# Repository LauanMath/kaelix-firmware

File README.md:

# Kaelix

O Kaelix mede a vibração de motores industriais com um transmissor de baixo
custo, fixado na carcaça do motor, que envia o sinal pelo rádio LoRa a um
*gateway* instalado no mesmo local. Este repositório guarda o *firmware* dos
dois dispositivos, os dados da coleta em campo de 2 de novembro de 2026 e as
análises de detecção de falhas feitas com esses dados e com uma base pública de
laboratório. A interface de programação de aplicações (API), o banco de dados e
o aplicativo de mesa que recebem os dados do *gateway* estão no repositório
[kaelix-industrial-intelligence](https://github.com/LauanMath/kaelix-industrial-intelligence).

O sistema foi desenvolvido no trabalho de conclusão de curso de Lauan Matheus
da Rocha Alves, em Engenharia de Software, no Instituto de Ensino Superior
iCEV, em 2026. A monografia está em [`docs/monografia/`](docs/monografia/).

## Sistema

O transmissor usa o microcontrolador ESP32-C3, o módulo MPU-6050, com
acelerômetro e giroscópio de três eixos, e o rádio Ra-02 (circuito SX1278) em
433 MHz. Em cada ciclo de medição, ele adquire uma janela de 512 amostras por
eixo a 1 kHz e envia pelo rádio uma telemetria, com indicadores calculados
sobre a janela e o estado do dispositivo. Quando o *gateway* autoriza, o
transmissor envia também a janela de sinal bruto dos seis canais, dividida em
26 fragmentos, e essa sequência de fragmentos é chamada de rajada. O *gateway*
informa quais fragmentos recebeu, e o transmissor reenvia só os ausentes, em
até três tentativas.

O *gateway* usa o ESP32-S3, com outro rádio Ra-02 e Wi-Fi, e envia os dados à
API por HTTPS, pela rede local. Cada telemetria e cada janela ficam gravadas na
memória *flash* do *gateway* até que a API confirme o recebimento. O
transmissor recebe pelo rádio, por meio do *gateway*, a configuração, a rotina
de medição e os comandos definidos no aplicativo. O *gateway* é configurado
pela rede Wi-Fi própria (`Kaelix-XXXX`) e recebe atualizações de *firmware*
pela rede; o transmissor só recebe *firmware* por cabo.

| Parte | Código | Ambiente do PlatformIO |
|---|---|---|
| Transmissor | `src/transmitter/`, `src/sensors/`, `src/power/` | `kaelix-transmitter` |
| *Gateway* | `src/gateway/`, com a pinagem e o *buffer* de logs de `src/receiver/` | `kaelix-gateway` |
| Protocolo de rádio v3 e CRC | `lib/kaelix_protocol/`, `lib/crc16/` | os dois |
| Processamento de sinal e códigos de estado | `lib/signal_processing/`, `lib/kaelix_status/` | transmissor |

## Compilação e gravação

Os dois ambientes compilam com o PlatformIO, na plataforma `espressif32` com o
*framework* Arduino, e o rádio usa a biblioteca RadioLib 7.7.1:

```bash
pio run -e kaelix-transmitter -t upload --upload-port <porta>
pio run -e kaelix-gateway -t upload --upload-port <porta>
```

O `platformio.ini` é o mesmo que compilou o *firmware* da coleta, em 2 de
novembro de 2026, e não foi editado depois. O resumo SHA-256 dele e dos fontes
do transmissor e do *gateway* identifica essa versão
([`build_sistema_values.py`](docs/monografia/latex/scripts/build_sistema_values.py)).
Por isso, o arquivo ainda declara sete ambientes de versões anteriores
(`esp32-s3`, `esp32-s3-bench`, `lora-probe`, `esp32-s3-gateway`,
`esp32-c3-device`, `esp32-c3-receiver` e `lora-probe-c3`), cujo código foi
removido do repositório. Os ambientes antigos não compilam, e `pio run` sem
`-e` termina com erro ao chegar a eles. O `kaelix-gateway` herda do `esp32-s3`
as configurações da placa.

## Testes

Os testes do *firmware* rodam no computador, sem os dispositivos:

```bash
pio test -e native
```

As sete suítes somam 64 casos e cobrem o protocolo, os registros e o gravador
do *gateway*, o *buffer* de logs, o CRC, o processamento de sinal e a aquisição
de vibração. A saída da execução de 7 de novembro de 2026, sobre o mesmo código
da coleta, está em `experiments/sistema/`.

## Dados e análises

A coleta em campo de 2 de novembro de 2026 mediu quatro máquinas de uma
instalação industrial em operação normal: uma dobradeira, uma guilhotina
hidráulica, uma calandra piramidal e um compressor de parafuso. Os dados foram
exportados do banco da API em modo somente leitura e estão em
`experiments/campo/dados/`. O resumo SHA-256 de `ensaios.csv`, `leituras.csv`,
`janelas.csv` e `janelas.npz` foi gravado no registro das hipóteses antes de
qualquer cálculo
([`registro_v1.md`](docs/monografia/registro/registro_v1.md)). O banco e os
registros dos ensaios ficam fora do repositório, porque trazem nomes de rede e
endereços do local, e por isso os scripts de exportação não rodam a partir
dele.

As hipóteses H1 a H3, avaliadas nos dados de campo, foram registradas em 6 de
novembro de 2026, antes do cálculo. Emendas datadas, também anteriores aos
cálculos que definem, acrescentaram a hipótese H4, avaliada na base pública de
desbalanceamento da Fraunhofer-Gesellschaft, e as análises posteriores AP1 a
AP6 (registros v2 a v4, em [`docs/monografia/registro/`](docs/monografia/registro/)).

| Script | Análise | Saídas |
|---|---|---|
| `experiments/campo/analise_registrada.py` | H1 a H3 | `experiments/campo/analise_registrada/` |
| `experiments/campo/analise_descritiva.py` | ruído do sensor, rotação, espectros, rajadas e resposta a mudanças de condição | `experiments/campo/analise_descritiva/` |
| `experiments/campo/analise_posterior.py` | AP1 e AP2 | `experiments/campo/analise_posterior/` |
| `experiments/fraunhofer/baixar_membros_v2.py` | download dos seis arquivos da base usados em H4, com conferência de CRC-32 e tamanho | `experiments/fraunhofer/dados/v2/`, fora do git |
| `experiments/fraunhofer/analise_h4.py` | H4 | `experiments/fraunhofer/analise_registrada/` |
| `experiments/campo/analise_posterior_v4.py` | AP3 a AP6, com os descritores calculados por `analise_h4.py` | `experiments/campo/analise_posterior_v4/` |

O cabeçalho de cada script traz o comando de execução, com as versões das
bibliotecas, e cada análise grava as versões usadas em `ambiente.json`, junto
com as saídas. Os comandos rodam a partir da raiz do repositório:

```bash
uv run --no-project --with numpy --with scipy --with scikit-learn python experiments/campo/analise_registrada.py
python3 -I experiments/fraunhofer/baixar_membros_v2.py
```

Os seis arquivos da base da Fraunhofer somam cerca de 4 GB. Os números da
monografia não são digitados: scripts gravam macros do LaTeX em
`docs/monografia/latex/values/`, e o
[`README.md` da monografia](docs/monografia/README.md) lista cada script e o
que ele confere. A monografia compila com `make` em `docs/monografia/latex/`,
com saída em `build/main.pdf`.

## Figuras

Os diagramas do sistema são gerados em R, com o tema de
`experiments/figures/scripts/theme_kaelix.R`, por exemplo com
`Rscript experiments/figures/scripts/fig12_implantacao.R`; com `FIG_ANON=1`, o
mesmo script gera a variante `fig12_implantacao_anon`, sem o nome do serviço na
rede local. As figuras com fotos de campo são montadas em Python a partir das
fotos originais, que ficam fora do repositório porque mostram a instalação
industrial. As saídas estão em `experiments/figures/output/`, e as figuras de
resultados da monografia são geradas por `docs/monografia/latex/figuras_src/`.

## Estrutura

```
kaelix-firmware/
├── platformio.ini          ambientes do PlatformIO
├── partitions/             tabela de partições do gateway
├── src/
│   ├── transmitter/        transmissor (ESP32-C3)
│   ├── gateway/            gateway (ESP32-S3)
│   ├── sensors/            aquisição de vibração
│   ├── power/              watchdog
│   └── receiver/           pinagem e buffer de logs usados pelo gateway
├── lib/                    protocolo v3, CRC, processamento de sinal e códigos de estado
├── test/                   testes do firmware no computador (PlatformIO e Unity)
├── tools/                  análise estática e testes sem o PlatformIO
├── experiments/
│   ├── campo/              dados e análises da coleta em campo
│   ├── fraunhofer/         download da base pública e análise de H4
│   ├── sistema/            saída dos testes do firmware de 7 de novembro de 2026
│   └── figures/            diagramas do sistema e fotos de campo
└── docs/monografia/        monografia em LaTeX, registro das hipóteses e auditoria do texto
```

## Estudos anteriores

Até 11 de novembro de 2026, o repositório também guardava o projeto das placas
e do invólucro, a análise térmica, um modelo de detecção embarcado treinado na
base MAFAULDA, versões anteriores do *firmware*, um simulador do enlace, uma
verificação formal em Lean 4 e a versão anterior da monografia. Os estudos
anteriores não entram na monografia atual e foram removidos da árvore de
arquivos, mas continuam no histórico do git: o commit `82548fd` é o último que
contém todos eles. O
[CHANGELOG](CHANGELOG.md) registra as mudanças.

## Limites

- O transmissor só recebe *firmware* por cabo e não grava as medições: uma
  janela medida com o *gateway* desligado se perde.
- Uma telemetria corrompida no ar não é reenviada. Sem ela, o *gateway* não
  autoriza a rajada, e a leitura e a janela daquele ciclo se perdem; a falta
  aparece como lacuna na sequência das telemetrias.
- Os comandos enviados pelo rádio são protegidos por CRC, sem autenticação.
- O sensor do módulo respondeu `0x74` ao registrador de identificação,
  diferente do `0x68` do MPU-6050, e a marcação do circuito integrado não foi
  conferida.
- O filtro passa-baixas digital do sensor foi configurado com banda nominal de
  184 Hz, abaixo dos 1000 Hz da faixa de medição da série ISO 10816. A
  velocidade eficaz calculada até 184 Hz é, por isso, um limite inferior da
  velocidade eficaz de banda larga.
- O transmissor não tem termistor (`KAELIX_HAS_NTC=0`), e a temperatura das
  telemetrias é a do próprio sensor.

## Licença

O código está sob a licença MIT ([LICENSE](LICENSE)). Os dados e os
resultados das análises estão sob a licença Creative Commons Atribuição 4.0
Internacional ([LICENSE-DADOS](LICENSE-DADOS)):

- `experiments/campo/dados/`: dados da coleta em campo de 2 de novembro de 2026;
- `experiments/campo/analise_registrada/`, `analise_descritiva/`,
  `analise_posterior/` e `analise_posterior_v4/`: resultados das análises da
  coleta;
- `experiments/fraunhofer/analise_registrada/`: descritores e resultados
  derivados da base pública da Fraunhofer, também CC BY 4.0; a atribuição e as
  modificações estão em `LICENSE-DADOS`;
- `docs/monografia/registro/`: registro das hipóteses e das emendas.

Mantêm a licença de origem:

- `docs/monografia/latex/abntex2-alf-2025.bst`: cópia modificada de
  `abntex2-alf.bst`, do abnTeX2, sob a LaTeX Project Public License 1.3 ou
  posterior;
- `docs/monografia/latex/imagens/logo-icev.jpg` e
  `docs/monografia/latex/preambulo/estilo-icev.tex`: logo e estilo do modelo de
  monografia do iCEV, que pertencem à instituição.

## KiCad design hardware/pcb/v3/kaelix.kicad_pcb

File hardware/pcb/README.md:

# Placa — versões

Projeto KiCad versionado por diretório. Cada versão é autocontida
(`.kicad_sch`, `.kicad_pcb`, `.kicad_pro`, `.kicad_sym`, `sym-lib-table` e
derivados) e é gerada por `hardware/gen_schematic.py` + `hardware/gen_pcb.py`.
Nenhum arquivo destas pastas é editado à mão.

```
KAELIX_PCB=v1 ./tools/build-hardware.sh        # v1 é o padrão
KAELIX_PCB=v2 ./tools/build-hardware.sh
KAELIX_PCB=v3 ./tools/build-hardware.sh
```

**O esquemático é idêntico na v1 e na v2.** Mesma netlist, mesmos 32
componentes, mesmos 24 nets. O que a v2 muda é o contorno, o placement e o
roteamento — consequência do vão do invólucro correspondente
(`hardware/involucro/README.md`), não decisão de circuito.

**A v3 é a primeira revisão de circuito:** a v2 mais a carga da bateria
(BQ21040 e USB-C). Até a v2 a placa não tinha como carregar a célula. Ver
[O que a v3 muda](#o-que-a-v3-muda).

| | v1 | v2 | v3 |
|---|---|---|---|
| estado | congelada | ativa até a v3 | ativa |
| invólucro | v1, vão 43 × 43 | v2, vão 62 × 52 | v3 = corpo da v2 com o furo do USB-C na altura do conector |
| contorno | 42 × 42, 4 recortes r = 6,0 | 61 × 51, 4 recortes r = 4,5 | igual à v2 |
| recortes entre eixos | 36,0 × 36,0 | 57,0 × 47,0 | igual à v2 |
| área útil de cobre | 1477 mm² | 2962 mm² (+101%) | igual à v2 |
| folga no vão | 0,50 mm/lado em X e Y | 0,50 mm/lado em X e Y | 0,50 mm/lado; em −X o USB-C passa 0,07 mm para dentro do furo da parede, por projeto |
| componentes | 32 + 3 furos M2 | 32 + 3 furos M2 | 41 + 3 furos M2 |
| nets · pads com net | 24 · 118 | 24 · 118 | 30 · 149 |
| segmentos | 485 (327 F.Cu / 159 B.Cu) | 501 (419 F.Cu / 83 B.Cu) | 647 (495 F.Cu / 152 B.Cu) |
| vias de sinal | 68 | 68 | 96 |
| vias de costura de terra | 71 | 234 | 222 |
| triedro M2 | 63°, 206°, 326° — menor separação **97°** | 79°, 199°, 319° — menor separação **120°** | 64°, 184°, 304° — menor separação **120°** |
| ângulos legais para furo | 89 de 360 | 171 de 360 | 181 de 360 |
| deslocamento máx. no placement | 13,50 mm | 4,00 mm | 11,25 mm |
| desacoplamento acima de 3 mm (reta) | **6 de 6** | **2 de 6** | **3 de 6** |
| pior caso | 11,08 mm (C8 → U3.3) | 4,47 mm (C8 → U3.3) | 5,90 mm (C3 → U1.2) |
| corredor do cabo da bateria | 4,0 mm | 6,0 mm | 6,0 mm |
| envelope montado | 42,00 × 42,00 × 13,42 mm | 61,00 × 51,00 × 13,42 mm | 61,58 × 51,00 × 13,42 mm (nariz do USB-C) |
| ERC | 0 violações | 0 violações | 0 violações |
| DRC | 0 regra, 0 desconectado | 0 regra, 0 desconectado | 0 regra, 0 desconectado |
| interferência 3D | nenhuma entre 92 corpos | nenhuma entre 92 corpos | nenhuma entre 116 corpos |

A linha de desacoplamento usava uma métrica antiga ("10 de 10", "3 de 10"),
anterior à correção 16a, que tirou da conta os quatro capacitores que não
desacoplam nada. Segmentos, vias e costura da v1 e da v2 mudaram com as
correções 27 e 28 abaixo, sem tocar em circuito nem em placement.

Regras de fabricação, iguais nas duas: traço 0,20 · folga 0,15 · via Ø0,60 com
furo 0,30 mm; mínimos declarados furo 0,20 · folga 0,15 · traço 0,15 mm.

## O que a v2 resolve

| Item | v1 | v2 | Causa |
|---|---|---|---|
| desacoplamento | 10 capacitores acima de 3 mm, pior 11,08 | 3 acima de 3 mm, pior 5,95 | Na v1 o Ra-02 fica empilhado sob o WROOM-1U e divide o mesmo anel; na v2 cada módulo tem canto próprio. Os deslocamentos da v2 também deixaram de ser palpite: saem do contorno do CI mais a folga de corpo mais a meia-largura da peça |
| corredor do cabo | 4,0 mm | 6,0 mm | Medido: com 6,0 mm a v1 perde a saída de GND de RT1.2 e R8.2 (3 itens soltos no DRC); a v2 tem área para o plano contornar o corredor |
| triedro de furos M2 | 97° | 120° | O acelerômetro apoiado num triedro assimétrico mede a flexão da própria placa. 171 ângulos legais contra 89 |
| retorno de sinal | 151 segmentos em B.Cu | 81 | Menos rasgos no plano de terra da face de baixo |
| bateria | nenhuma célula de catálogo entra no invólucro v1 | célula real de 2000 mAh, 265 dias | Ver `hardware/involucro/README.md`, defeitos #5 e #6 |

## O que a v2 **não** muda

Eletrônica. Nenhum componente, valor, net ou conexão difere. Os dois
`.kicad_sch` têm os mesmos 294 elementos e 12 símbolos. Isso é deliberado: a
v2 é uma revisão mecânica e de layout, e misturá-la com mudança de circuito
tornaria impossível atribuir qualquer diferença de comportamento medido.

## O que a v3 muda

Circuito, pela primeira vez desde a v1: a placa passa a **carregar a
bateria**. Até a v2 não havia CI carregador nem conector de entrada — o
invólucro tinha o furo de USB-C, os relatórios falavam em "recarga por USB-C",
e a netlist não. Fonte: bloco `COM_CARGA` em `hardware/gen_schematic.py`.

| Peça | Função | Por quê |
|---|---|---|
| U5 BQ21040 (SOT-23-6) | carregador linear de uma célula, 4,2 V | único entre BQ21040, TP4056 e MCP73831 com monitor de temperatura da **célula** pronto para NTC de 10 k |
| RT2 NTC 10k β 3380 | TS do U5: suspende a carga acima de 45 °C (V_TS < 275 mV) e abaixo de 0 °C (V_TS > 1250 mV) | limiares do BQ21040 calibrados para β ≈ 3370 (103AT-2); o B3950 do RT1 cortaria perto de 39 °C |
| R13 2k7 | I_carga = K_ISET / R_ISET = 540 / 2,7 k = 200 mA | escolhida pelo modelo térmico, ver abaixo |
| J3 USB-C só energia, R11/R12 5k1 | entrada de 5 V | Rd em CC1 e CC2 é o que faz fonte C-para-C entregar VBUS |
| C13, C14 1 µF; C15 220 nF | entrada, saída e filtro do TS | C15 é opcional na folha de dados; aqui não, porque o RT2 fica a 22 mm do U5, na placa do rádio |
| IO7 ← CHG_N | status da carga para o firmware | GPIO de RTC: pode acordar do deep sleep; sem pull-up externo |

O limite de 45 °C que a análise térmica usa deixa de ser recomendação da
folha de dados da célula e passa a ser **imposto pelo hardware**.

**Corrente de carga, do modelo térmico.** O BQ21040 é linear e dissipa
I·(V_USB − V_bat) dentro do invólucro fechado. `hardware/termica_carga.py`
roda o FEM de `termica.py` com essa fonte interna: a placa sobe
**~15 K por watt**. Pior ponto da corrente constante (V_bat = 3,0 V), V_USB =
5,0 V, ambiente 30 °C. Com o motor a 90 °C a placa fica entre a média da
parede e o equilíbrio radiativo com o piso quente (+3,2 K, seção térmica de
`hardware/fem/README.md`); os dois extremos estão na tabela:

| I | P | bancada | motor frio | motor a 90 °C | carga completa |
|---|---|---|---|---|---|
| 150 mA | 0,30 W | 35,1 °C | 35,0 °C | 39,6 – 42,8 °C | ~15 h |
| **200 mA** | **0,41 W** | **36,7 °C** | **36,6 °C** | **41,1 – 44,3 °C** | **~12 h** |
| 250 mA | 0,51 W | 38,3 °C | 38,2 °C | 42,6 – 45,8 °C — TS pode cortar | ~9 h |
| 500 mA | 1,04 W | 46,6 °C — TS corta | 46,4 °C — TS corta | 50,2 – 53,4 °C — TS corta | — |

A 200 mA sobram 8,3 K até o corte na bancada ou com o motor parado. **No
motor a 90 °C sobram entre 0,7 e 3,9 K**: a carga funciona, mas no limite, e
com ambiente acima de 30 °C a margem cai kelvin por kelvin. Quem decide é o
TS, que suspende a carga e a retoma ao esfriar — é a proteção funcionando,
não falha. O procedimento recomendado é carregar fora do motor ou com ele
parado. Tudo isto é modelo, não medição, e a folga do motor quente é
otimista: a resistência interna herdada usa o h externo, e a convecção dentro
da cavidade é mais fraca. Ali a folga real pode ser nula. Hipóteses em
`hardware/termica_carga.py` e `hardware/fem/README.md`.

**Placement.** J3 na borda −X, alinhado ao furo do invólucro; U5 e os passivos
na face de baixo, sob o J3. RT2 na face de cima, sob a célula e longe do U5. O
J1 desce 3 mm em relação à v2: na posição antiga o corpo dele invadia o do J3
em 3,77 × 2,47 mm.

**Conector de borda.** O corpo do USB-C passa da borda da placa por projeto.
O gerador passou a conhecer isso (`NA_BORDA`): o encaixe é conferido pelos
pads, a linha "PCB Edge" do footprint tem de cair na borda (desvio medido
0,000 mm), e a passagem pela parede é interseção de sólidos em
`gen_involucro.py`.

## Defeitos de projeto identificados

### Fechados

| # | Defeito | Medição | Correção |
|---|---|---|---|
| 1 | Corte de energia dos periféricos por BC337 low-side. Os pull-ups de 4k7 permaneciam em +3V3 e alimentavam o MPU6050 pelos diodos de ESD de SDA/SCL | FM-27 em `docs/ANALISE-DE-FALHAS.md` | load switch high-side (Q1 SI2301 + Q2 BC847B); pull-ups movidos para o rail comutado +3V3_SW |
| 2 | MPU6050 permanentemente alimentado: 3,9 mA contínuos | orçamento em `src/power/sleep.cpp` | passou ao rail comutado; 314 µA efetivos |
| 3 | Placa em Ø74 mm num vão de 43. `verifica_encaixe` passava porque comparava escalares | contorno contra o vão do desenho | módulos empilhados um por face; contorno retangular |
| 4 | Ângulo de pad gravado como relativo. É **absoluto** (biblioteca + rotação do footprint) | 42 curtos no DRC | conferido contra as placas de exemplo do KiCad |
| 5 | Sinal da rotação invertido: pad local (0; 7,62) a 90° ia para −x | pad 4 do J2 aparecia em +7,62 no DRC | corrigido |
| 6 | Rotação própria do pad ignorada | QFN-24 descrito com pads de 0,85 mm num passo de 0,5 — sobrepostos entre si | escape do barramento I2C passou a fechar |
| 7 | Pad `custom` medido pelo `size` (âncora) | aba do SOT-89 tem 4,6 mm; o `size` diz 1,475 | quatro pistas passavam por cima da aba |
| 8 | Colisão mecânica e colisão de cobre tratadas como um invariante só | furo M2 sobre o pad do R6 não era detectado | separadas; passante vale nas duas faces |
| 9 | Nenhuma pista roteada — só footprints, planos e contorno | 70 pads desconectados no DRC | roteador de labirinto de duas camadas |
| 10 | Sem medição de tensão da bateria | REQ-SEG-29, REQ-SEG-53 e o heartbeat da QUARENTENA dependem dela | divisor 1M/1M + C11 em IO6 |
| 11 | Sem proteção de polaridade invertida na entrada | — | Q3 SI2301 em série, dreno na bateria |
| 12 | Sem filtro no nó do ADC do NTC. FM-08 raciocina sobre "capacitância de filtro × 10 k" — capacitor que não existia | `docs/ANALISE-DE-FALHAS.md` | C12 100n |
| 13 | Corredor de cabo do conector de bateria não modelado; furo M2 a 2,6 mm da boca | courtyard cobre a peça, não o que se conecta nela | corredor virou restrição de placement |
| 14 | Varredura do corredor registrada em comentário estava obsoleta: atribuía o limite ao triedro de furos e a peças sem lugar | remedido: placement fecha de 2,0 a 9,0 mm, furos a 97° em toda a faixa | o limite real é o plano de terra; comentário reescrito com o número medido |
| 15 | `gen_involucro.py` conferia as duas cavidades contra uma única versão de placa, escolhida por variável de ambiente | v1 do invólucro acusava 1616 mm³ de interferência com a placa da v2 | a placa passou a acompanhar a versão do invólucro |
| 22 | Nenhum caminho de carga da bateria: sem carregador, sem conector de entrada | netlist; o furo USB-C do invólucro não tinha conector | v3: BQ21040 + USB-C. v1 e v2 ficam como estão |
| 27 | Pino passante de peça não contava como obstáculo na face oposta. Só furo de fixação contava | DRC da v3: 3 `pth_inside_courtyard` — pinos de carcaça do J3 sob U5, R13 e C14 | a regra de furo passou a valer para pino (pad ≥ 0,8 mm). Via térmica de 0,6 mm continua de fora: o Ra-02 da v1 assenta sob as do WROOM-1U por projeto |
| 28 | O roteador contava como plano a faixa entre as fileiras de pads de um QFN de passo fino | DRC da v3: grupo de GND solto — o escape do U2.1 terminava numa ilha sob o MPU6050 | sob o corpo de peça de passo fino, na face dela, o plano não conta como caminho (`router.py`, `sob_fino`). Mudou o roteamento da v1 e da v2 também; as duas continuam com DRC limpo |
| 29 | Os furos de USB-C e SMA nunca foram cortados no modelo do invólucro | o cilindro começava fora do corpo, em −cx em vez de −cx/2 | ver `hardware/involucro/README.md` |
| 35 | O roteador punha via sobre via e via dentro de pino passante. Cada par de pads era roteado à parte, e duas ligações da mesma net que trocavam de camada no mesmo ponto emitiam duas vias; nada impedia trocar de camada sobre o pad de um pino passante | DRC da v3 com avisos: 10 pares de vias empilhadas, vias de UART_TX e UART_RX a 0,2 mm do centro dos pinos 3 e 4 do J2, e pares de VBUS e VBAT com furos a 0 e 0,1 mm. O `build-hardware.sh` só lia erros, e no KiCad 10 isso é aviso | via nova a pelo menos furo + folga de furo (0,55 mm) de outra, reaproveitando a que está exatamente no ponto, e nunca sobre pino passante (`router.py`, `_perto_de_via` e `sem_via`). A v3 caiu de 108 para 96 vias de sinal. O `build-hardware.sh` agora reprova `hole_to_hole` e `holes_co_located` mesmo como aviso. **A v1 e a v2 não foram regeradas**: os arquivos versionados ainda têm 5 e 9 avisos de furo, e regerá-las muda o roteamento das duas |
| 36 | As 12 vias térmicas do pad do WROOM-1U vinham da biblioteca com furo de 0,2 mm, o único da placa abaixo de 0,3 | furo de 0,2 mm em placa de 2 camadas: a JLCPCB e a PCBWay cobram à parte ou seguram o pedido na revisão de engenharia | todo furo metalizado sai com pelo menos `FURO_MIN` = 0,3 mm, e o gerador aborta se o anel ficar abaixo de 0,15 mm (`gen_pcb.py`, `alarga_furo`). Pad de 0,6 mm com furo de 0,3 dá o mesmo anel das vias; entre as vias térmicas sobram 0,69 mm de furo a furo. Roteamento inalterado |

### Abertos

| # | Defeito | v1 | v2 | Decorrência |
|---|---|---|---|---|
| 16 | Desacoplamento acima de 3 mm do pino, em linha reta | 6 de 6, pior 11,08 mm | 2 de 6, pior 4,47 mm | Restam C8 (4,47) e C3 (3,30). C8 é o segundo capacitor de um **único** pino de +3V3 do Ra-02: em 0805 não há terceira posição |
| 16a | A métrica contava quatro capacitores que não desacoplam nada | lista antiga: C1, C5, C6, C9 | idem | C1 é o RC do EN, C5 e C6 são o regulador interno e a bomba de carga do MPU6050 (exigência de folha de dados, não de PDN) e C9 é a entrada do LDO. `_DESACOPLA` corrigido para C2, C3, C4, C7, C8, C10 |
| 16b | **A régua mede a reta; o laço vê a pista.** Numa placa de 2 camadas o retorno está a 1,5 mm, o que dá 781 pH/mm de pista e 1,30 nH por via passante | C8: 11,1 mm em reta contra **36,1 mm de pista e 6 vias** → 35,9 nH (3,25×) | pior caso C3: 6,4 mm de pista e 2 vias → 7,59 nH | A distância euclidiana subestimava a indutância por até 3,25×. Ver `hardware/pdn.py` e a figura 9 |
| 16c | **A v2 aproximou os capacitores e piorou o PDN.** O roteador pôs 2 vias no caminho do capacitor de bulk do ESP32-S3 | Z abaixo do alvo de 733 mΩ em toda a faixa | passa do alvo acima de **6,0 MHz** (ESP32-S3) e de **1,1 MHz** (MPU6050) | Ganho de placement em linha reta não se traduziu em ganho elétrico. Corrigir pede fixar o caminho do bulk na mesma face, sem via |
| 17 | Cinco pads de sinal do WROOM-1U a 1,27 mm de passo não comportam seis discretos a 3 mm | — | — | 0805 em pé pede 3,5 mm de passo. Limite de encapsulamento, não de área |
| 18 | Corredor do cabo | 4,0 mm | 6,0 mm | A v1 não aceita os ~6 mm que um alojamento PHR-2 com chicote pede |
| 19 | Altura dominada pelos **conectores**: J2 tem 11,54 mm e J1 tem 5,60, contra 3,20 dos módulos | igual | igual | Num dispositivo selado, um header de gravação de 11,5 mm é a peça mais alta. Decidir se fica populado no produto |
| 20 | Divisor do NTC satura no frio: nó chega a 3,22 V a −40 °C, acima da faixa útil do ADC (~3,1 V a 12 dB) | igual | igual | Abaixo de ~−35 °C a leitura sai otimista e **não** dispara os limiares de curto/aberto (ratio 0,94 contra 0,99). Inverter o divisor refaz toda a derivação de limiares |
| 21 | Numeração de pino do HT7333 em SOT-89-3 varia por fabricante | igual | igual | Conferir contra a folha de dados antes de fabricar |
| 22a | Furo USB-C Ø13,0 no invólucro sem conector correspondente | igual | igual | Fechado na v3 (J3). Na v1 e na v2 o furo existe no corpo e segue sem conector |
| 30 | v3: o NTC do TS lê a **placa**, não a célula | — | — | A placa fica acima da célula durante a carga, então o corte vem cedo, nunca tarde. Célula com NTC próprio (3 fios) tiraria a folga |
| 31 | v3: célula invertida **e** USB ligado ao mesmo tempo | — | — | O carregador sobe VBAT, liga o Q3 e injeta a pré-carga na célula invertida até VBAT cair abaixo do Vgs(th). Exige falha dupla; o JST-PH é polarizado. Saída em VBAT_RAW seria pior: a célula invertida conduziria pelo ESD do OUT mesmo sem USB |
| 32 | v3: nenhum código lê o CHG_N | — | — | O hardware está no IO7; o firmware ainda não sabe se está carregando |
| 33 | v3: modo próprio, PDN e vibração não foram recalculados | — | — | Contorno, furos e módulos são os da v2; as nove peças novas são estimadas em menos de 2 g. Declarado, não medido |
| 34 | v3: sem TVS no VBUS | — | — | O BQ21040 aguenta 30 V na entrada e desliga acima de 6,65 V (OVP). Descarga eletrostática no conector não está tratada |
| 23 | Rabicho u.FL → SMA fora da BOM | igual | igual | O Ra-02 tem IPEX; a ligação ao painel não está especificada |
| 24 | Não há código lendo a tensão da bateria | igual | igual | O caminho de hardware existe (IO6, divisor, capacitor); os limiares de REQ-SEG-29 não estão implementados |
| 26 | Modo próprio da placa cai 32% na v2 (2001 → 1352 Hz) e, a fs = 1000 Hz, dobra para 352 Hz | modal FEM em `hardware/fem/README.md` | Continua acima dos 1000 Hz da ISO nas duas versões, mas é mais um item que o DLPF do MPU6050 tem de rejeitar — configuração ainda pendente em `vibration_init` |
| 25 | A placa não parafusa nos bosses do invólucro em nenhuma das versões | furo M3 em (18; 18) pediria material até 28,2 mm na diagonal; o canto R7 da cavidade termina em 27,5 | recortes r=4,5 ficam exatamente sobre os eixos dos bosses | A fixação é o assento pelo aro mais os três M2 próprios. Os bosses seguram a tampa, não a placa |

## O que a geração verifica

- ERC com aviso tratado como erro
- DRC com zonas preenchidas; violação de regra é falha dura, item desconectado
  é contado contra linha de base declarada (**zero** nas três versões)
- furação: furo sobre furo ou encostado (`hole_to_hole`, `holes_co_located`)
  é falha dura, mesmo sendo aviso no KiCad 10
- contenção no contorno e colisão entre peças, separadas em mecânica e cobre
- distância de cada capacitor de desacoplamento ao pino que serve
- existência e validade de cada modelo 3D referenciado
- envelope, o que define a altura, interferência entre corpos e folga contra o
  vão da versão correspondente do invólucro
- derivados regerados a cada execução: netlist, BOM, STEP, renders

## Não verificado

- Se a pinagem confere com a peça física
- Numeração de pino do HT7333 em SOT-89-3
- Desempenho de RF, consumo real e qualquer medida de bancada
- Se o roteamento sobrevive à montagem: o gerador prova regras, não fabricação

## Reprodutibilidade

Apagando todos os derivados e regerando, `.kicad_sch`, `.kicad_pcb` e
`.kicad_sym` voltam **byte a byte idênticos**. O roteador é determinístico.

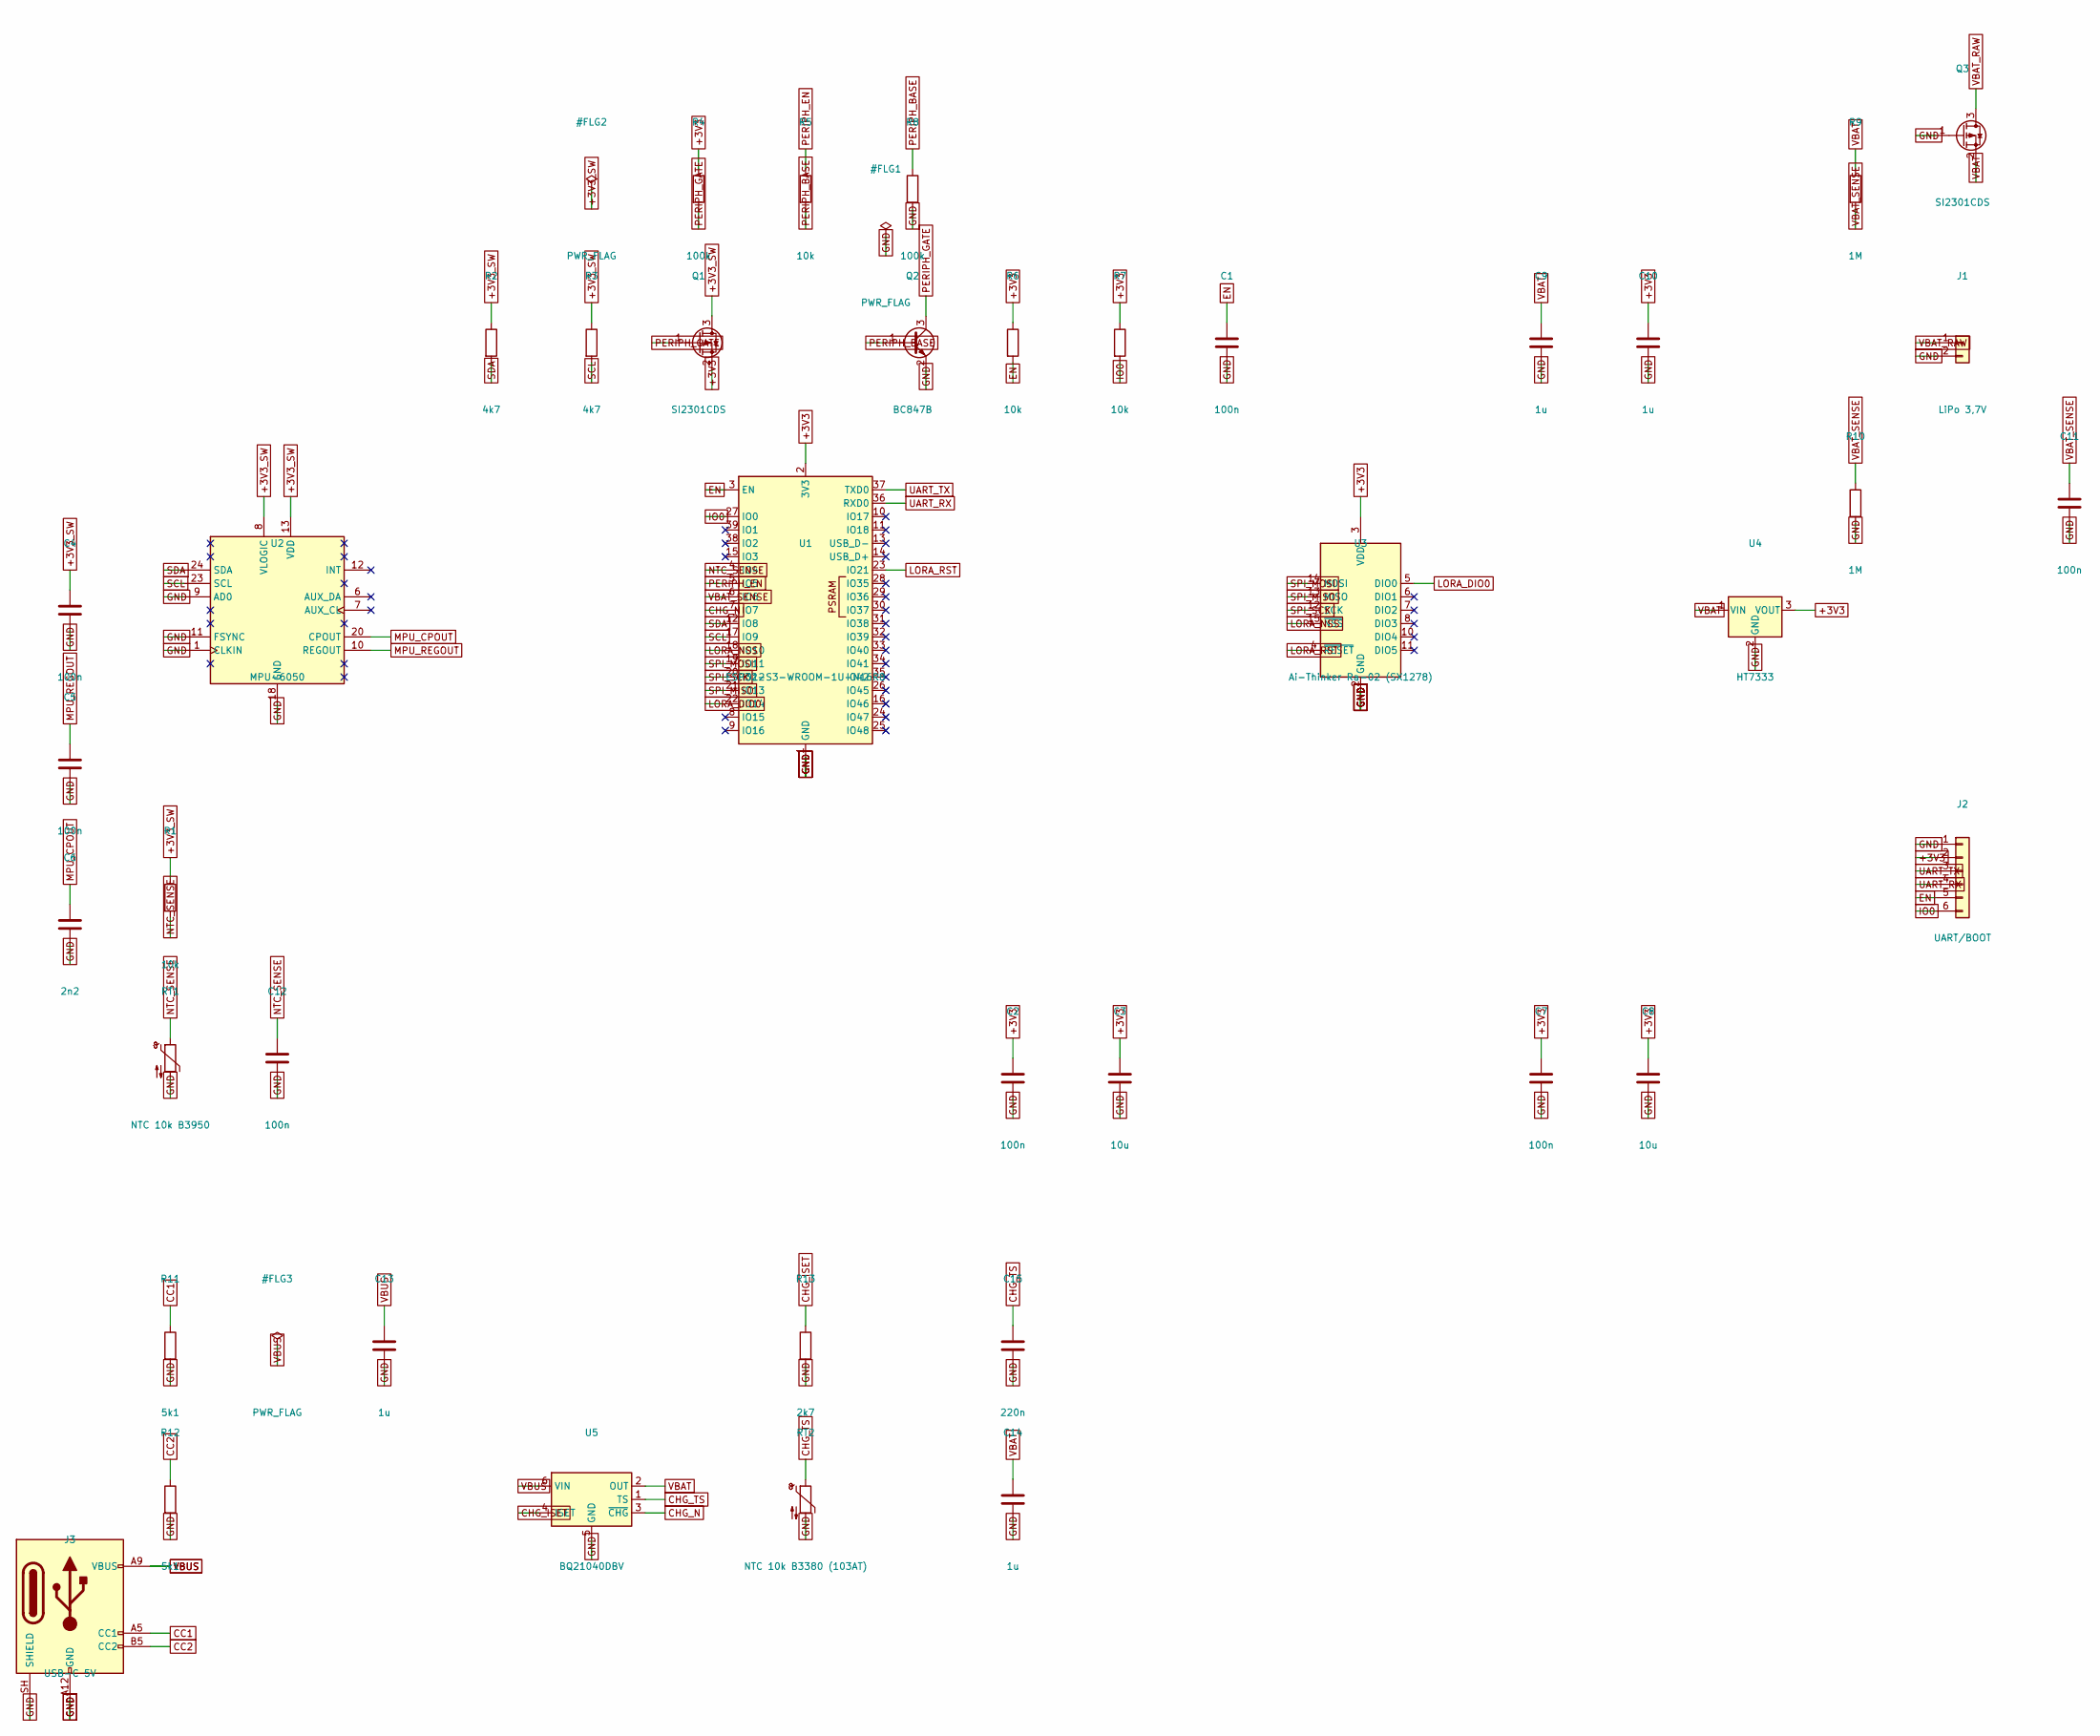
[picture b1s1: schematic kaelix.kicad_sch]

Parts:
C1, C2, C4, C5, C7, C11, C12: 100n; C_0805_2012Metric
C3, C8: 10u; C_0805_2012Metric
C6: 2n2; C_0805_2012Metric
C9, C10, C13, C14: 1u; C_0805_2012Metric
C15: 220n; C_0805_2012Metric
J1: LiPo 3,7V; JST_PH_S2B-PH-SM4-TB_1x02-1MP_P2.00mm_Horizontal
J2: UART/BOOT; PinHeader_1x06_P2.54mm_Vertical
J3: USB-C 5V; USB_C_Receptacle_GCT_USB4125-xx-x_6P_TopMnt_Horizontal
Q1, Q3: SI2301CDS; SOT-23
Q2: BC847B; SOT-23
R1, R5, R6, R7: 10k; R_0805_2012Metric
R2, R3: 4k7; R_0805_2012Metric
R4, R8: 100k; R_0805_2012Metric
R9, R10: 1M; R_0805_2012Metric
R11, R12: 5k1; R_0805_2012Metric
R13: 2k7; R_0805_2012Metric
RT1: NTC 10k B3950; R_0805_2012Metric
RT2: NTC 10k B3380 (103AT); R_0805_2012Metric
U1: ESP32-S3-WROOM-1U-N16R8; ESP32-S3-WROOM-1U
U2: MPU-6050; InvenSense_QFN-24_4x4mm_P0.5mm
U3: Ai-Thinker Ra-02 (SX1278); Ai-Thinker-Ra-01-LoRa
U4: HT7333; SOT-89-3
U5: BQ21040DBV; SOT-23-6

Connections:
+3V3: C2.1, C3.1, C7.1, C8.1, C10.1, J2.2, Q1.2 (S), R4.1, R6.1, R7.1, U1.2 (3V3), U3.3 (VDD), U4.3 (VOUT)
+3V3_SW: C4.1, Q1.3 (D), R1.1, R2.1, R3.1, U2.8 (VLOGIC), U2.13 (VDD)
CC1: J3.A5 (CC1), R11.1
CC2: J3.B5 (CC2), R12.1
CHG_ISET: R13.1, U5.4 (ISET)
CHG_N: U1.7 (IO7), U5.3 (~CHG)
CHG_TS: C15.1, RT2.1, U5.1 (TS)
EN: C1.1, J2.5, R6.2, U1.3 (EN)
GND: C1.2, C2.2, C3.2, C4.2, C5.2, C6.2, C7.2, C8.2, C9.2, C10.2, C11.2, C12.2, C13.2, C14.2, C15.2, J1.2, J2.1, J3.A12 (GND), J3.B12 (GND), J3.SH (SHIELD), Q2.2 (E), Q3.1 (G), R8.2, R10.2, R11.2, R12.2, R13.2, RT1.2, RT2.2, U1.1 (GND), U1.40 (GND), U1.41 (GND), U2.1 (CLKIN), U2.9 (AD0), U2.11 (FSYNC), U2.18 (GND), U3.1 (GND), U3.2 (GND), U3.9 (GND), U3.16 (GND), U4.2 (GND), U5.5 (GND)
IO0: J2.6, R7.2, U1.27 (IO0)
LORA_DIO0: U1.22 (IO14), U3.5 (DIO0)
LORA_NSS: U1.18 (IO10), U3.15 (~NSS)
LORA_RST: U1.23 (IO21), U3.4 (~RESET)
MPU_CPOUT: C6.1, U2.20 (CPOUT)
MPU_REGOUT: C5.1, U2.10 (REGOUT)
NTC_SENSE: C12.1, R1.2, RT1.1, U1.4 (IO4)
PERIPH_BASE: Q2.1 (B), R5.2, R8.1
PERIPH_EN: R5.1, U1.5 (IO5)
PERIPH_GATE: Q1.1 (G), Q2.3 (C), R4.2
SCL: R3.2, U1.17 (IO9), U2.23 (SCL)
SDA: R2.2, U1.12 (IO8), U2.24 (SDA)
SPI_MISO: U1.21 (IO13), U3.13 (MISO)
SPI_MOSI: U1.19 (IO11), U3.14 (MOSI)
SPI_SCK: U1.20 (IO12), U3.12 (SCK)
UART_RX: J2.4, U1.36 (RXD0)
UART_TX: J2.3, U1.37 (TXD0)
VBAT: C9.1, C14.1, Q3.2 (S), R9.1, U4.1 (VIN), U5.2 (OUT)
VBAT_RAW: J1.1, Q3.3 (D)
VBAT_SENSE: C11.1, R9.2, R10.1, U1.6 (IO6)
VBUS: C13.1, J3.A9 (VBUS), J3.B9 (VBUS), U5.6 (VIN)

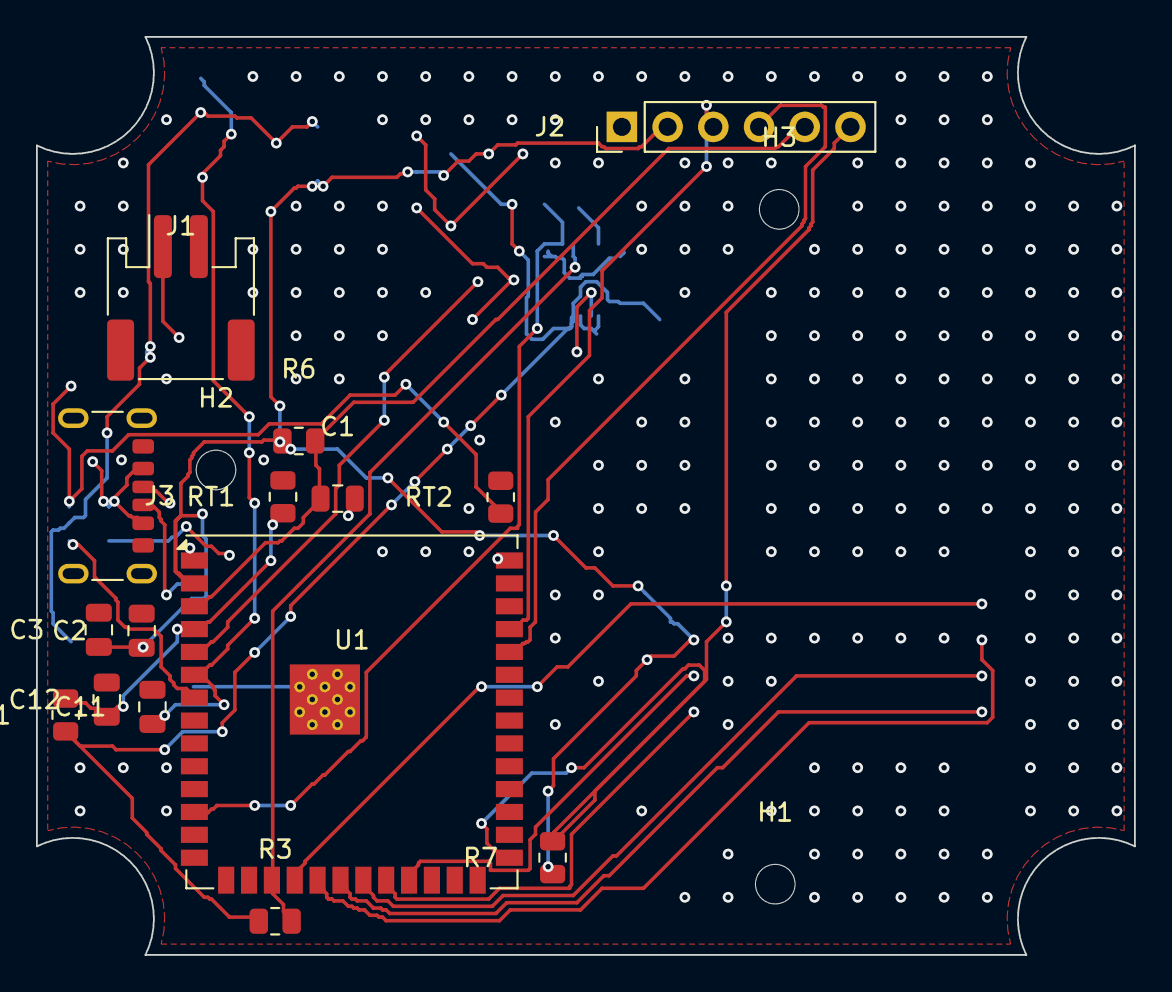
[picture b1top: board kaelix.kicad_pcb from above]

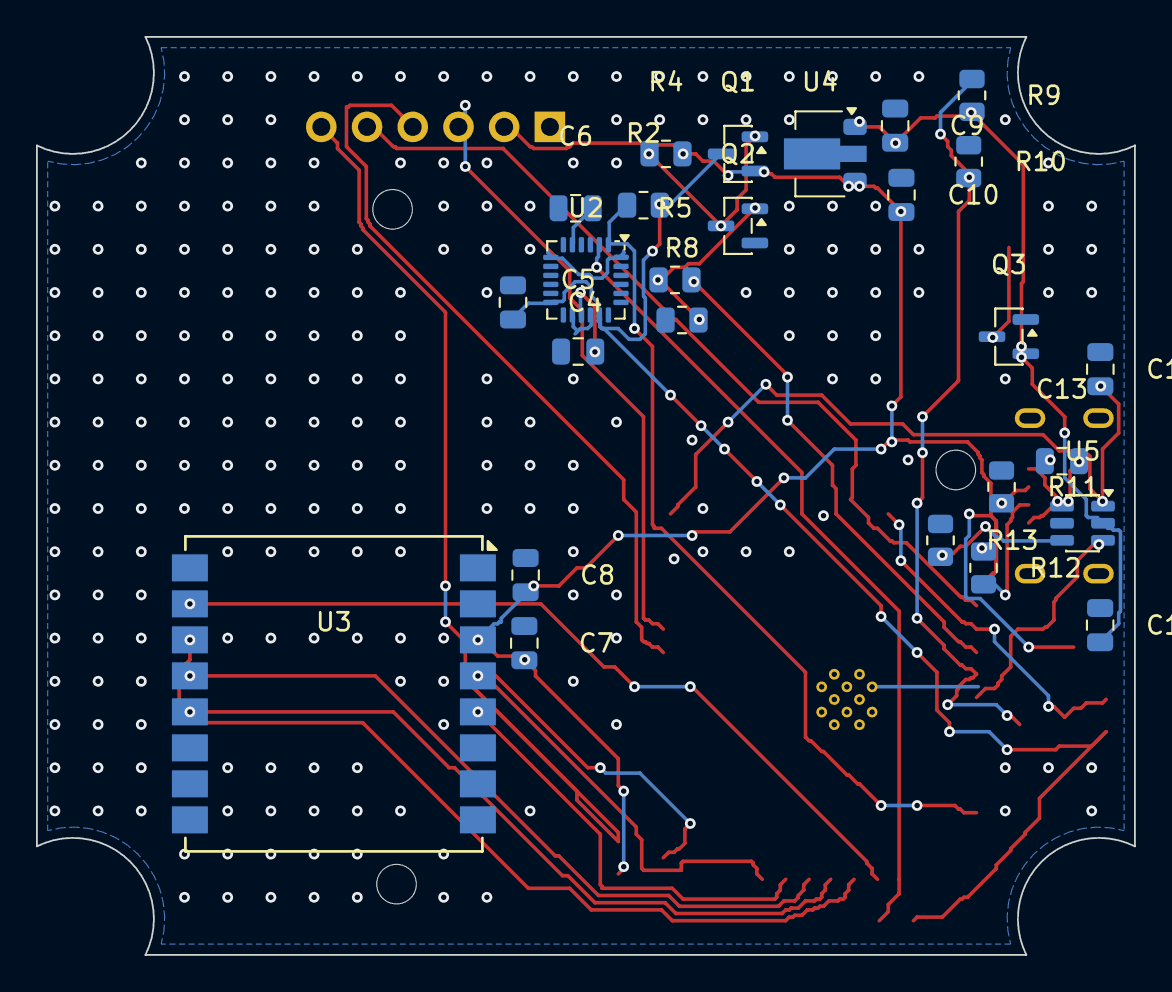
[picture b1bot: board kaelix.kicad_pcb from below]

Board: 2 copper layers, 61.0 x 51.0 mm, 44 parts (26 on the bottom side), 30 nets.

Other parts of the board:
H1, H2, H3: M2; MountingHole_2.2mm_M2

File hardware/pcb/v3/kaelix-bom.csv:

"Reference","Value","Footprint"
"C1,C2,C4,C5,C7,C11,C12","100n","Capacitor_SMD:C_0805_2012Metric"
"C3,C8","10u","Capacitor_SMD:C_0805_2012Metric"
"C6","2n2","Capacitor_SMD:C_0805_2012Metric"
"C9,C10,C13,C14","1u","Capacitor_SMD:C_0805_2012Metric"
"C15","220n","Capacitor_SMD:C_0805_2012Metric"
"J1","LiPo 3,7V","Connector_JST:JST_PH_S2B-PH-SM4-TB_1x02-1MP_P2.00mm_Horizontal"
"J2","UART/BOOT","Connector_PinHeader_2.54mm:PinHeader_1x06_P2.54mm_Vertical"
"J3","USB-C 5V","Connector_USB:USB_C_Receptacle_GCT_USB4125-xx-x_6P_TopMnt_Horizontal"
"Q1,Q3","SI2301CDS","Package_TO_SOT_SMD:SOT-23"
"Q2","BC847B","Package_TO_SOT_SMD:SOT-23"
"R1,R5-R7","10k","Resistor_SMD:R_0805_2012Metric"
"R2,R3","4k7","Resistor_SMD:R_0805_2012Metric"
"R4,R8","100k","Resistor_SMD:R_0805_2012Metric"
"R9,R10","1M","Resistor_SMD:R_0805_2012Metric"
"R11,R12","5k1","Resistor_SMD:R_0805_2012Metric"
"R13","2k7","Resistor_SMD:R_0805_2012Metric"
"RT1","NTC 10k B3950","Resistor_SMD:R_0805_2012Metric"
"RT2","NTC 10k B3380 (103AT)","Resistor_SMD:R_0805_2012Metric"
"U1","ESP32-S3-WROOM-1U-N16R8","RF_Module:ESP32-S3-WROOM-1U"
"U2","MPU-6050","Sensor_Motion:InvenSense_QFN-24_4x4mm_P0.5mm"
"U3","Ai-Thinker Ra-02 (SX1278)","RF_Module:Ai-Thinker-Ra-01-LoRa"
"U4","HT7333","Package_TO_SOT_SMD:SOT-89-3"
"U5","BQ21040DBV","Package_TO_SOT_SMD:SOT-23-6"
